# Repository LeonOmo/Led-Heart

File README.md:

# Led Heart

A heart shaped PCB with 10 Leds which run in a loop. Build with an NE555 and a 4017.

## Why does it exist?

- Christmas: Its a present made for christmas, hence christmas is approching i wanted to make some gifts.
- Dependence on Microcontrollers: I almost always just use microcontrollers so i made something without one.

## Features

- No Code needed
- Heart Shaped PCB
- Adjustable loop Speed

## Components

| Reference | Component |
| :--- | :--- |
| U1 | 4017 |
| U2 | NE555P |
| D1 to D10 | LEDs |
| R1 | 470 resistor |
| R2 | 1k resistor |
| RV1 | 50k potentiometer (speed) |
| C1 | 1 µF capacitor |
| C2 | 0.01 µF capacitor |
| J1, J2 | Power pads (5 V and GND) |
| PCB | Custom heart PCB |

## Tools

- KiCAD: For the PCB Design

## Schematic

## PCB

## Extras

- Credits: Omocat (pixelart on my PCB not in the files)

## Bonus

There was i time i had no idea what i was doing. 

Something i added to the PCB as an example of what you can put on.

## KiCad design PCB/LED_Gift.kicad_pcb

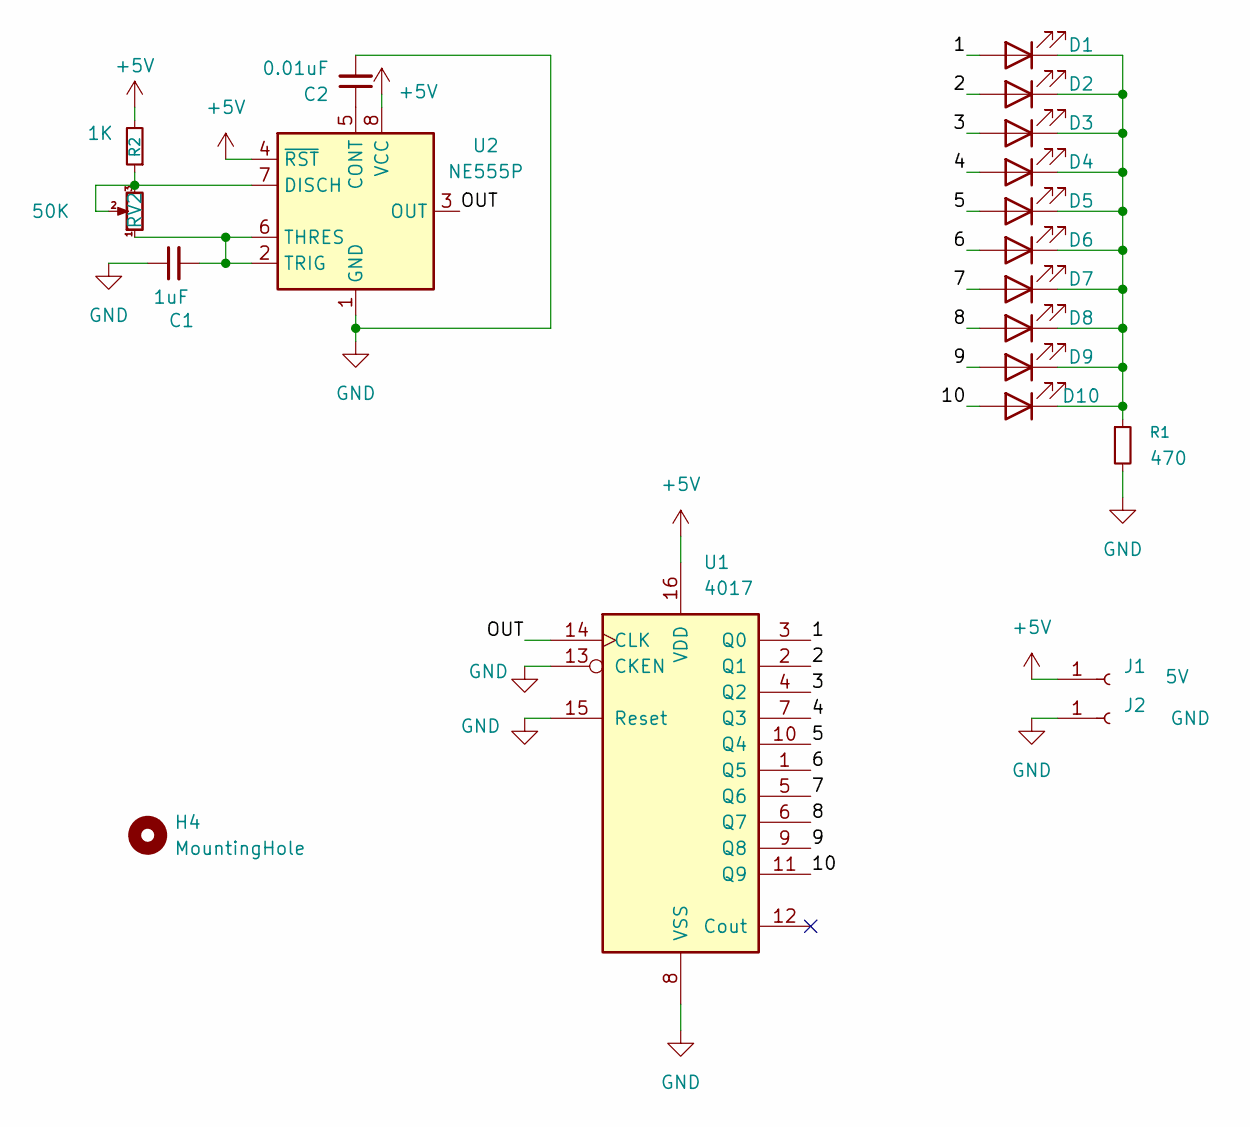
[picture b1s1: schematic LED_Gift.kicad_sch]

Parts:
C1: 1uF; CP_Radial_D5.0mm_P2.00mm
C2: 0.01uF; C_Disc_D7.5mm_W2.5mm_P5.00mm
D1, D2, D3, D4, D5, D6, D7, D8, D9, D10: LED; LED_D3.0mm
H4: MountingHole; MountingHole_3.5mm
J1: 5V; TestPoint_Pad_2.5x2.5mm
J2: GND; TestPoint_Pad_2.5x2.5mm
R1: 470; R_Axial_DIN0207_L6.3mm_D2.5mm_P7.62mm_Horizontal
R2: 1K; R_Axial_DIN0207_L6.3mm_D2.5mm_P7.62mm_Horizontal
RV2: 50K; Potentiometer_Vishay_T93YA_Vertical
U1: 4017; N16
U2: NE555P; DIP-8_W7.62mm

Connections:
+5V: J1.1 (Pin_1_1), R2.2, U1.16 (VDD), U2.4 (~RST), U2.8 (VCC)
/1: D1.2 (A), U1.3 (Q0)
/2: D2.2 (A), U1.2 (Q1)
/3: D3.2 (A), U1.4 (Q2)
/4: D4.2 (A), U1.7 (Q3)
/5: D5.2 (A), U1.10 (Q4)
/6: D6.2 (A), U1.1 (Q5)
/7: D7.2 (A), U1.5 (Q6)
/8: D8.2 (A), U1.6 (Q7)
/9: D9.2 (A), U1.9 (Q8)
/10: D10.2 (A), U1.11 (Q9)
/OUT: U1.14 (CLK), U2.3 (OUT)
GND: C1.1, C2.2, J2.1 (Pin_1_1), R1.2, U1.8 (VSS), U1.13 (CKEN), U1.15 (Reset), U2.1 (GND)
unnamed: D1.1 (K), D2.1 (K), D3.1 (K), D4.1 (K), D5.1 (K), D6.1 (K), D7.1 (K), D8.1 (K), D9.1 (K), D10.1 (K), R1.1
unnamed: C2.1, U2.5 (CONT)
unnamed: R2.1, RV2.2, RV2.3, U2.7 (DISCH)
unnamed: C1.2, RV2.1, U2.2 (TRIG), U2.6 (THRES)

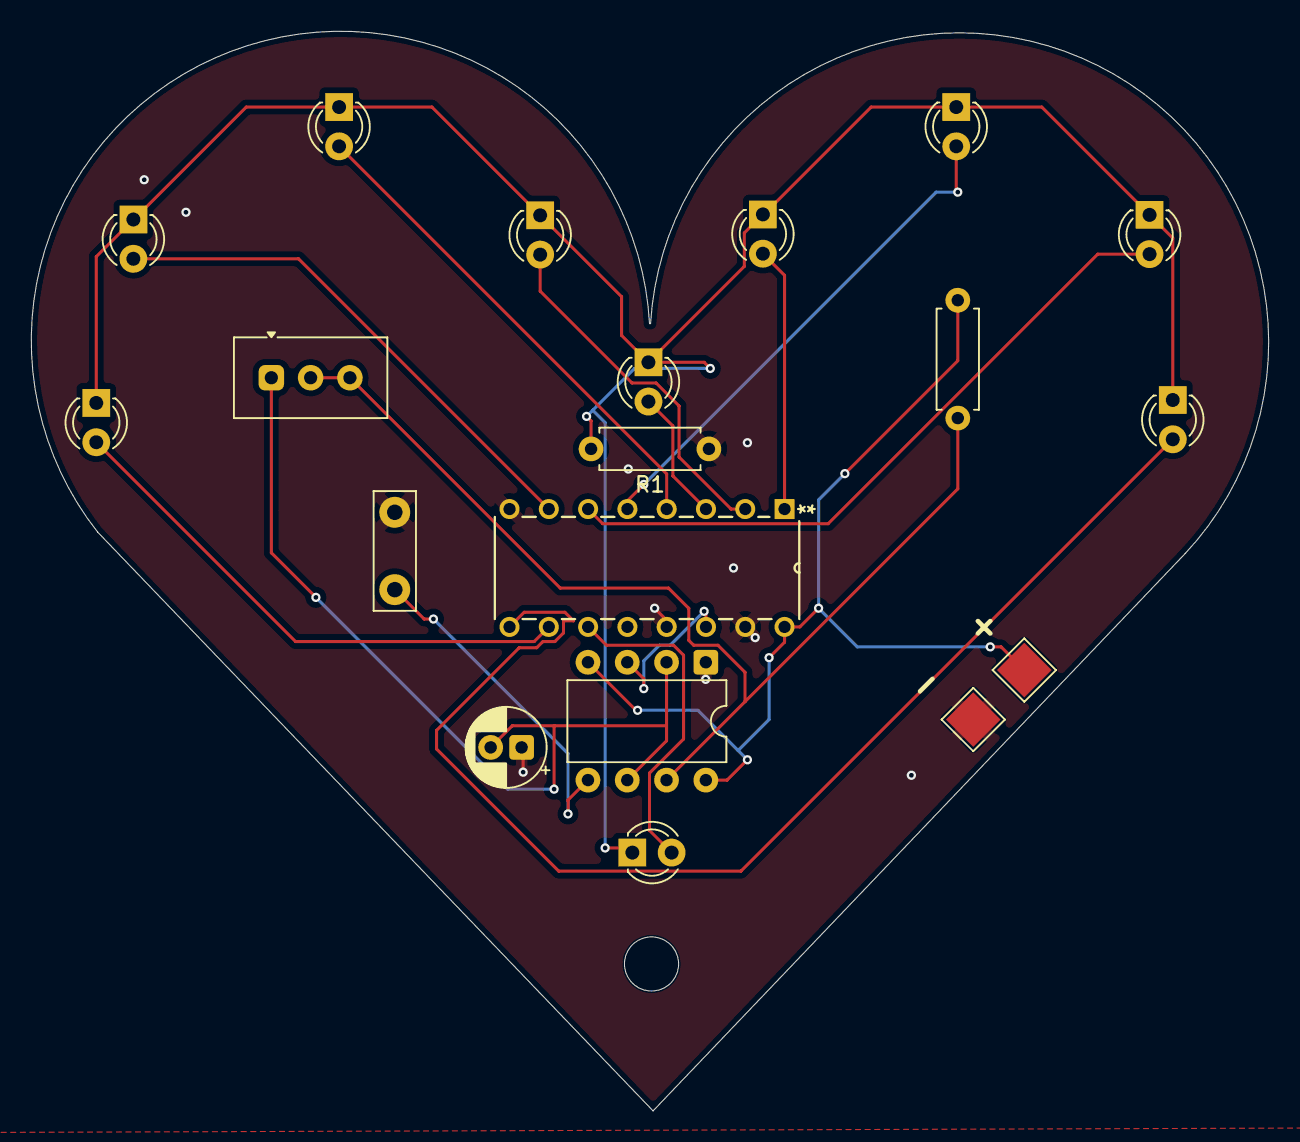
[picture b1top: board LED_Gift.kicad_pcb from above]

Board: 2 copper layers, 80.0 x 69.8 mm, 20 parts (0 on the bottom side), 17 nets.

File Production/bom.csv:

Designator,Footprint,Quantity,Value,LCSC Part #
C1,CP_Radial_D5.0mm_P2.00mm,1,1uF,
C2,C_Disc_D7.5mm_W2.5mm_P5.00mm,1,0.01uF,
"D1, D10, D2, D3, D4, D5, D6, D7, D8, D9",LED_D3.0mm,10,LED,
J1,TestPoint_Pad_2.5x2.5mm,1,5V,
J2,TestPoint_Pad_2.5x2.5mm,1,GND,
R1,R_Axial_DIN0207_L6.3mm_D2.5mm_P7.62mm_Horizontal,1,470,
R2,R_Axial_DIN0207_L6.3mm_D2.5mm_P7.62mm_Horizontal,1,1K,
RV2,Potentiometer_Vishay_T93YA_Vertical,1,50K,
U1,N16,1,4017,
U2,DIP-8_W7.62mm,1,NE555P,
